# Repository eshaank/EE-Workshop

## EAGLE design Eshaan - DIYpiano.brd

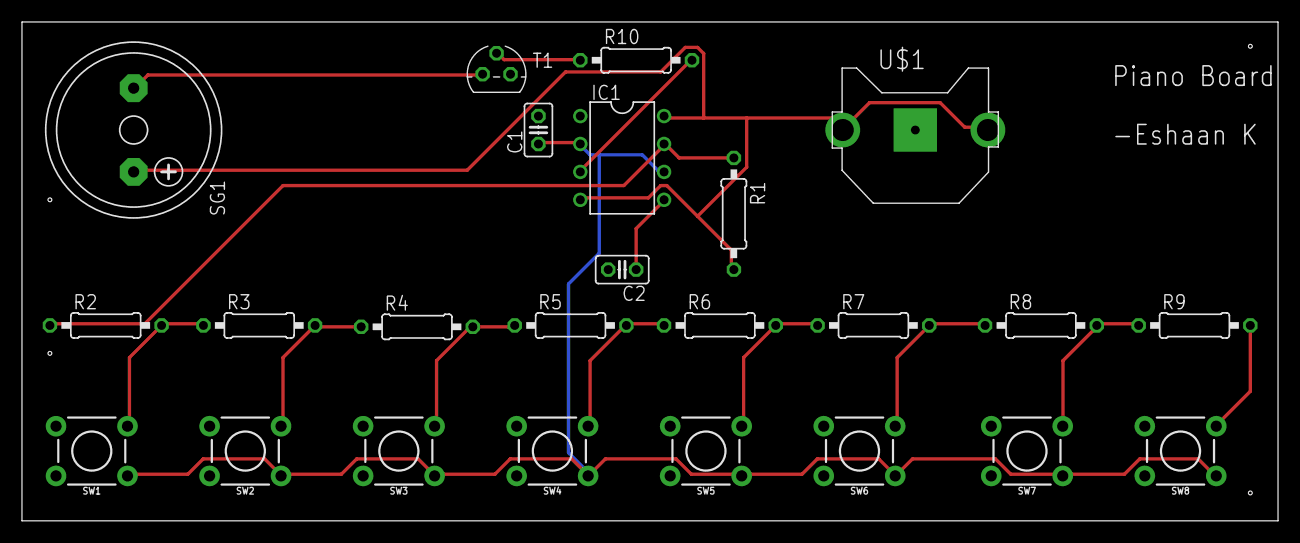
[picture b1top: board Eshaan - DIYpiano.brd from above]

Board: 2 copper layers, 114.3 x 45.4 mm, 24 parts (0 on the bottom side), 16 nets.

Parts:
C1: 100n; C025-025X050
C2: 100nF; C025-025X050
IC1: NE555N; DIL08
R1, R5, R10: 1K; 0207/10
R2: 6.2K; 0207/10
R3: 390; 0207/10
R4: 910; 0207/10
R6: 1.1K; 0207/10
R7: 620; 0207/10
R8: 1.3K; 0207/10
R9: 1.5K; 0207/10
SG1: F/HMB
SW1, SW2, SW3, SW4, SW5, SW6, SW7, SW8: MOMENTARY-SWITCH-SPST-PTH-6.0MM; TACTILE_SWITCH_PTH_6.0MM
T1: TO92
U$1: CR1220-THM

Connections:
GND: C1.2, C2.2, IC1.1, T1.1, U$1.-
unnamed: R2.2, R3.1, SW1.3
unnamed: IC1.7, R1.1, R2.1
unnamed: C1.1, IC1.2, IC1.6, SW1.1, SW2.1, SW3.1, SW4.1, SW5.1, SW6.1, SW7.1, SW8.1
unnamed: R3.2, R4.1, SW2.3
unnamed: R4.2, R5.1, SW3.3
unnamed: R5.2, R6.1, SW4.3
unnamed: R6.2, R7.1, SW5.3
unnamed: R7.2, R8.1, SW6.3
unnamed: R8.2, R9.1, SW7.3
unnamed: R9.2, SW8.3
unnamed: IC1.3, R10.2
unnamed: SG1.-, T1.3
unnamed: R10.1, T1.2
unnamed: C2.1, IC1.5
VCC: IC1.4, IC1.8, R1.2, SG1.+, U$1.+1, U$1.+2

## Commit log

2018-12-01 started DIYpiano
2018-12-15 Eshaan DIYpiano
    Finished the schematics for the DIYpiano.

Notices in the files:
parts and their libraries:
SparkFun-Switches: Licensing: Creative Commons ShareAlike 4.0 International - https://creativecommons.org/licenses/by-sa/4.0
